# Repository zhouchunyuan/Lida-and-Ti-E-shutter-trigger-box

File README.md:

# Lida-and-Ti-E-shutter-trigger-box
schematic and PCB

The project is created by kiCad 4.04

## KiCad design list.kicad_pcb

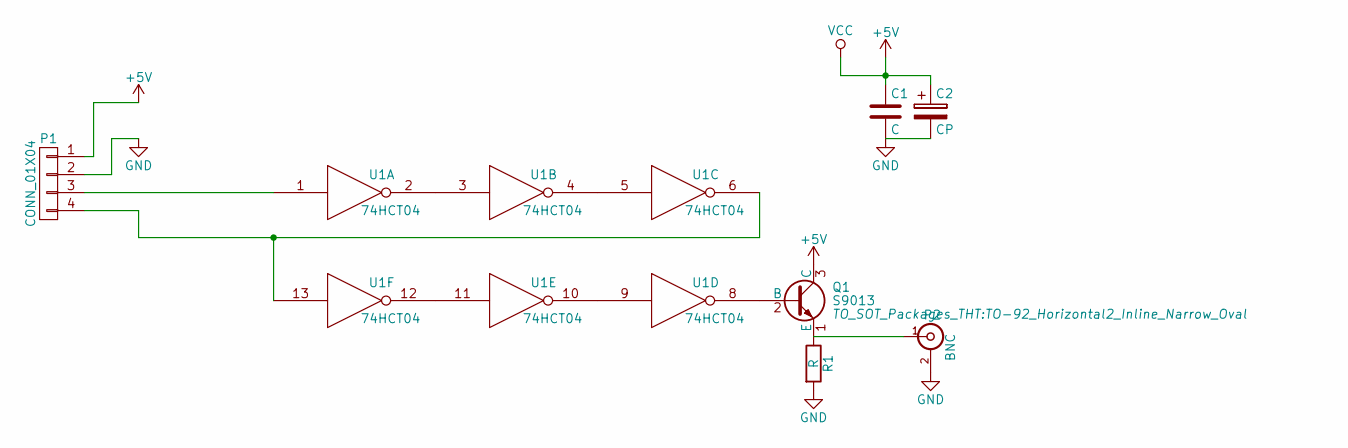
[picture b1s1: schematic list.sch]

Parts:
C1: C; C_Radial_D5_L11_P2.5
C2: CP; C_Disc_D3_P2.5
P1: CONN_01X04; bornier4
P2: BNC; bnc
Q1: S9013; TO-92_Horizontal2_Inline_Narrow_Oval
R1: R; Resistor_Horizontal_RM7mm
U1: 74HCT04; SOIC-14_3.9x8.7mm_Pitch1.27mm

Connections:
+5V: C1.1, C2.1, P1.1, Q1.3 (C), U1.14 (VCC)
GND: C1.2, C2.2, P1.2, P2.2 (Ext), R1.2, U1.7 (GND)
unnamed: P1.3, U1.1
unnamed: P1.4, U1.6, U1.13
unnamed: P2.1 (In), Q1.1 (E), R1.1
unnamed: Q1.2 (B), U1.8
unnamed: U1.2, U1.3
unnamed: U1.4, U1.5
unnamed: U1.9, U1.10
unnamed: U1.11, U1.12

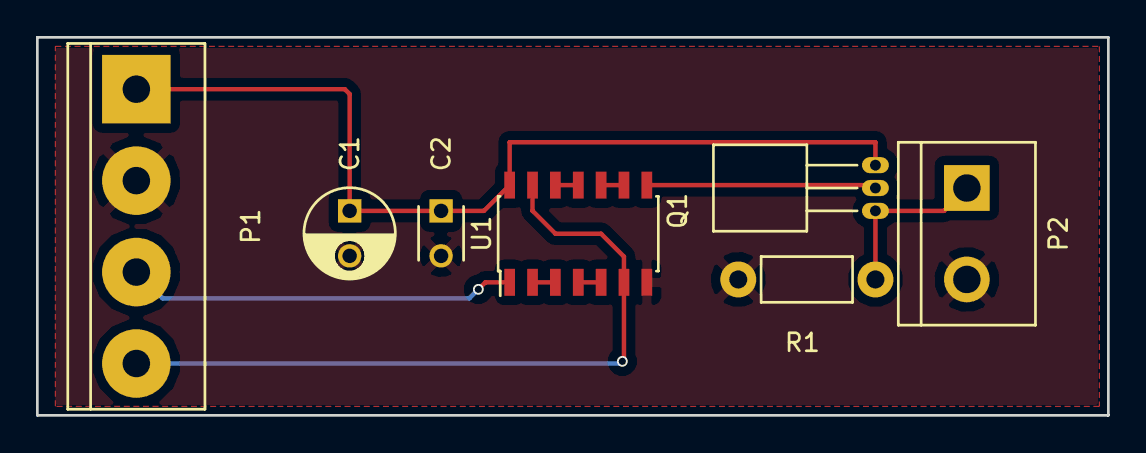
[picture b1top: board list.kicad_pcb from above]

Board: 2 copper layers, 59.5 x 21.0 mm, 7 parts (0 on the bottom side), 10 nets.
